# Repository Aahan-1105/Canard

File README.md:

# Canard
Canard70 is my custom 70-key keybard in a 65% form factor! It features hotswappable MX switches, wireless use, month long battery life (estimated) and more!

I created it because I was done with my current clicky keyboard and wanted something with a split spacebar inspired by split ergo keyboards.

## Features:
- Wireless
- Month+ Battery Life
- 65% form factor
- Split Spacebar (4 keys) and extra customizable buttons
- MacBook inspired layout for easy interoperability
- PCB mounted stabilizers
- Minimalist design!

## Images:
### Schematic Design:

### PCB Layout with Traces:

### PCB Render:

### Case CAD:

## Thanks!

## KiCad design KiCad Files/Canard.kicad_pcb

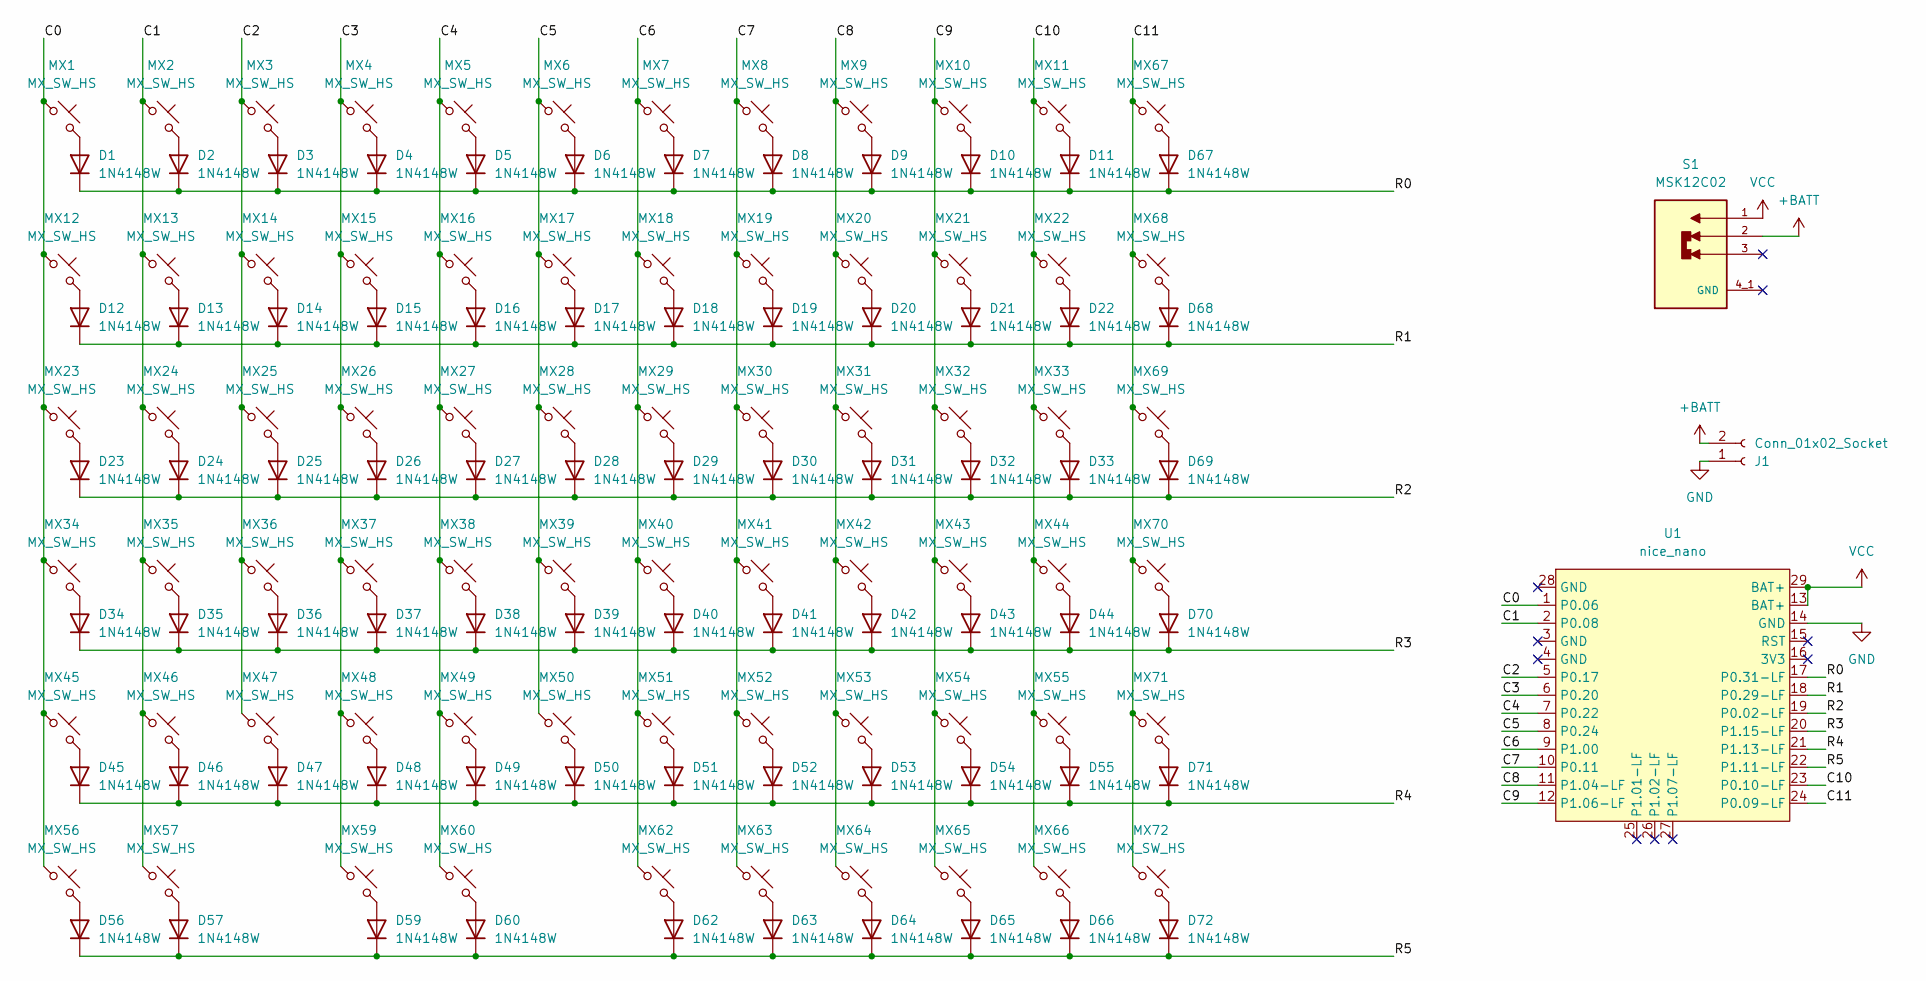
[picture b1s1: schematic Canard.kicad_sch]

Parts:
D1, D2, D3, D4, D5, D6, D7, D8, D9, D10, D11, D12, D13, D14, D15, D16, D17, D18, D19, D20, D21, D22, D23, D24, D25, D26, D27, D28, D29, D30, D31, D32, D33, D34, D35, D36, D37, D38, D39, D40, D41, D42, D43, D44, D45, D46, D47, D48, D49, D50, D51, D52, D53, D54, D55, D56, D57, D59, D60, D62, D63, D64, D65, D66, D67, D68, D69, D70, D71, D72: 1N4148W; D_SOD-123
J1: Conn_01x02_Socket; JST_PH_S2B-PH-K_1x02_P2.00mm_Horizontal
MX1, MX2, MX3, MX4, MX5, MX6, MX7, MX8, MX9, MX10, MX11, MX12, MX13, MX14, MX15, MX16, MX17, MX18, MX19, MX20, MX21, MX22, MX23, MX24, MX25, MX26, MX27, MX28, MX29, MX30, MX31, MX32, MX33, MX34, MX35, MX36, MX37, MX38, MX39, MX40, MX41, MX42, MX43, MX44, MX45, MX46, MX47, MX48, MX49, MX50, MX51, MX52, MX53, MX54, MX55, MX56, MX57, MX59, MX60, MX62, MX63, MX64, MX65, MX66, MX67, MX68, MX69, MX70, MX71, MX72: MX_SW_HS; SW_MX_HS_CPG151101S11_1u
S1: MSK12C02; SW_MSK12C02; PARTREV A/0
U1: nice_nano; nice_nano_AH_USBup

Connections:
+BATT: J1.2, S1.2
/C0: MX1.1, MX12.1, MX23.1, MX34.1, MX45.1, MX56.1, U1.1 (P0.06)
/C1: MX2.1, MX13.1, MX24.1, MX35.1, MX46.1, MX57.1, U1.2 (P0.08)
/C2: MX3.1, MX14.1, MX25.1, MX36.1, MX47.1, U1.5 (P0.17)
/C3: MX4.1, MX15.1, MX26.1, MX37.1, MX48.1, MX59.1, U1.6 (P0.20)
/C4: MX5.1, MX16.1, MX27.1, MX38.1, MX49.1, MX60.1, U1.7 (P0.22)
/C5: MX6.1, MX17.1, MX28.1, MX39.1, MX50.1, U1.8 (P0.24)
/C6: MX7.1, MX18.1, MX29.1, MX40.1, MX51.1, MX62.1, U1.9 (P1.00)
/C7: MX8.1, MX19.1, MX30.1, MX41.1, MX52.1, MX63.1, U1.10 (P0.11)
/C8: MX9.1, MX20.1, MX31.1, MX42.1, MX53.1, MX64.1, U1.11 (P1.04-LF)
/C9: MX10.1, MX21.1, MX32.1, MX43.1, MX54.1, MX65.1, U1.12 (P1.06-LF)
/C10: MX11.1, MX22.1, MX33.1, MX44.1, MX55.1, MX66.1, U1.23 (P0.10-LF)
/C11: MX67.1, MX68.1, MX69.1, MX70.1, MX71.1, MX72.1, U1.24 (P0.09-LF)
/R0: D1.1 (K), D2.1 (K), D3.1 (K), D4.1 (K), D5.1 (K), D6.1 (K), D7.1 (K), D8.1 (K), D9.1 (K), D10.1 (K), D11.1 (K), D67.1 (K), U1.17 (P0.31-LF)
/R1: D12.1 (K), D13.1 (K), D14.1 (K), D15.1 (K), D16.1 (K), D17.1 (K), D18.1 (K), D19.1 (K), D20.1 (K), D21.1 (K), D22.1 (K), D68.1 (K), U1.18 (P0.29-LF)
/R2: D23.1 (K), D24.1 (K), D25.1 (K), D26.1 (K), D27.1 (K), D28.1 (K), D29.1 (K), D30.1 (K), D31.1 (K), D32.1 (K), D33.1 (K), D69.1 (K), U1.19 (P0.02-LF)
/R3: D34.1 (K), D35.1 (K), D36.1 (K), D37.1 (K), D38.1 (K), D39.1 (K), D40.1 (K), D41.1 (K), D42.1 (K), D43.1 (K), D44.1 (K), D70.1 (K), U1.20 (P1.15-LF)
/R4: D45.1 (K), D46.1 (K), D47.1 (K), D48.1 (K), D49.1 (K), D50.1 (K), D51.1 (K), D52.1 (K), D53.1 (K), D54.1 (K), D55.1 (K), D71.1 (K), U1.21 (P1.13-LF)
/R5: D56.1 (K), D57.1 (K), D59.1 (K), D60.1 (K), D62.1 (K), D63.1 (K), D64.1 (K), D65.1 (K), D66.1 (K), D72.1 (K), U1.22 (P1.11-LF)
GND: J1.1, U1.14 (GND)
unnamed: D1.2 (A), MX1.2
unnamed: D2.2 (A), MX2.2
unnamed: D3.2 (A), MX3.2
unnamed: D4.2 (A), MX4.2
unnamed: D5.2 (A), MX5.2
unnamed: D6.2 (A), MX6.2
unnamed: D7.2 (A), MX7.2
unnamed: D8.2 (A), MX8.2
unnamed: D9.2 (A), MX9.2
unnamed: D10.2 (A), MX10.2
unnamed: D11.2 (A), MX11.2
unnamed: D12.2 (A), MX12.2
unnamed: D13.2 (A), MX13.2
unnamed: D14.2 (A), MX14.2
unnamed: D15.2 (A), MX15.2
unnamed: D16.2 (A), MX16.2
unnamed: D17.2 (A), MX17.2
unnamed: D18.2 (A), MX18.2
unnamed: D19.2 (A), MX19.2
unnamed: D20.2 (A), MX20.2
unnamed: D21.2 (A), MX21.2
unnamed: D22.2 (A), MX22.2
unnamed: D23.2 (A), MX23.2
unnamed: D24.2 (A), MX24.2
unnamed: D25.2 (A), MX25.2
unnamed: D26.2 (A), MX26.2
unnamed: D27.2 (A), MX27.2
unnamed: D28.2 (A), MX28.2
unnamed: D29.2 (A), MX29.2
unnamed: D30.2 (A), MX30.2
unnamed: D31.2 (A), MX31.2
unnamed: D32.2 (A), MX32.2
unnamed: D33.2 (A), MX33.2
unnamed: D34.2 (A), MX34.2
unnamed: D35.2 (A), MX35.2
unnamed: D36.2 (A), MX36.2
unnamed: D37.2 (A), MX37.2
unnamed: D38.2 (A), MX38.2
unnamed: D39.2 (A), MX39.2
unnamed: D40.2 (A), MX40.2
unnamed: D41.2 (A), MX41.2
unnamed: D42.2 (A), MX42.2
unnamed: D43.2 (A), MX43.2
unnamed: D44.2 (A), MX44.2
unnamed: D45.2 (A), MX45.2
unnamed: D46.2 (A), MX46.2
unnamed: D47.2 (A), MX47.2
unnamed: D48.2 (A), MX48.2
unnamed: D49.2 (A), MX49.2
unnamed: D50.2 (A), MX50.2
unnamed: D51.2 (A), MX51.2
unnamed: D52.2 (A), MX52.2
unnamed: D53.2 (A), MX53.2
unnamed: D54.2 (A), MX54.2
unnamed: D55.2 (A), MX55.2
unnamed: D56.2 (A), MX56.2
unnamed: D57.2 (A), MX57.2
unnamed: D59.2 (A), MX59.2
unnamed: D60.2 (A), MX60.2
unnamed: D62.2 (A), MX62.2
unnamed: D63.2 (A), MX63.2
unnamed: D64.2 (A), MX64.2
unnamed: D65.2 (A), MX65.2
unnamed: D66.2 (A), MX66.2
unnamed: D67.2 (A), MX67.2
unnamed: D68.2 (A), MX68.2
unnamed: D69.2 (A), MX69.2
unnamed: D70.2 (A), MX70.2
unnamed: D71.2 (A), MX71.2
unnamed: D72.2 (A), MX72.2
VCC: S1.1, U1.13 (BAT+), U1.29 (BAT+)

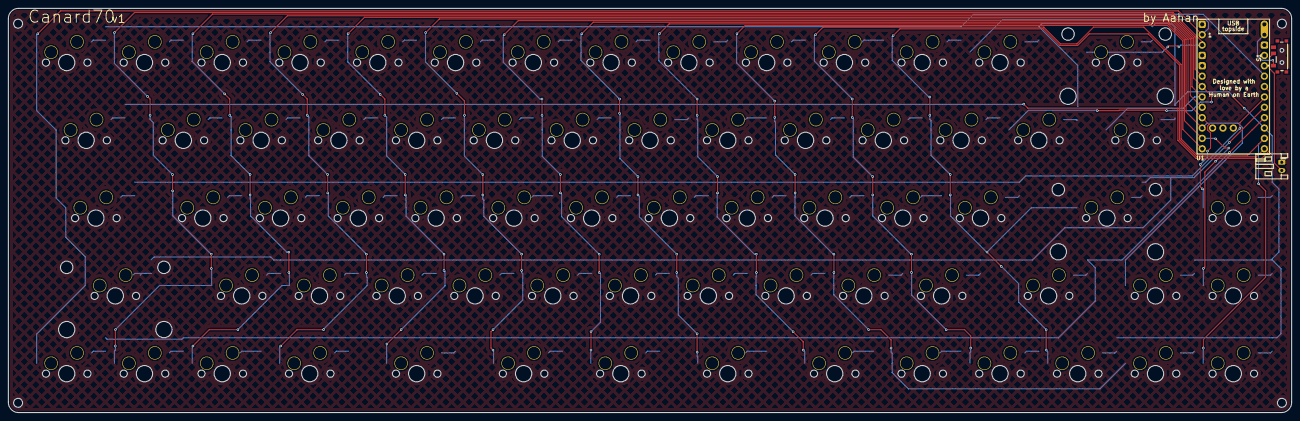
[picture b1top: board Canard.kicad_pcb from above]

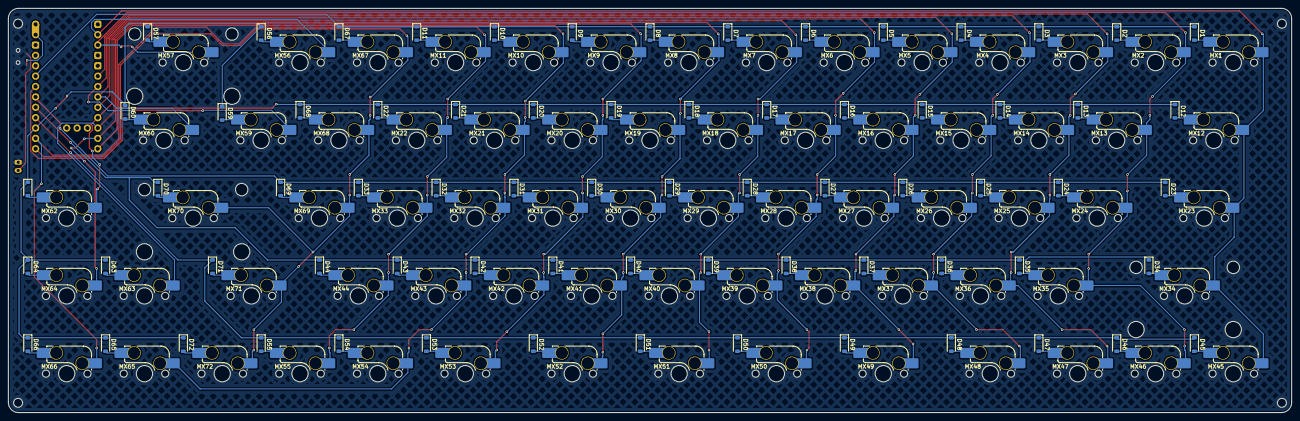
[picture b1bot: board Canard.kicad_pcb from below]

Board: 2 copper layers, 314.3 x 99.0 mm, 143 parts (140 on the bottom side), 91 nets.
